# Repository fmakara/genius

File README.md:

# genius
Jogo Genius do Mural do PET

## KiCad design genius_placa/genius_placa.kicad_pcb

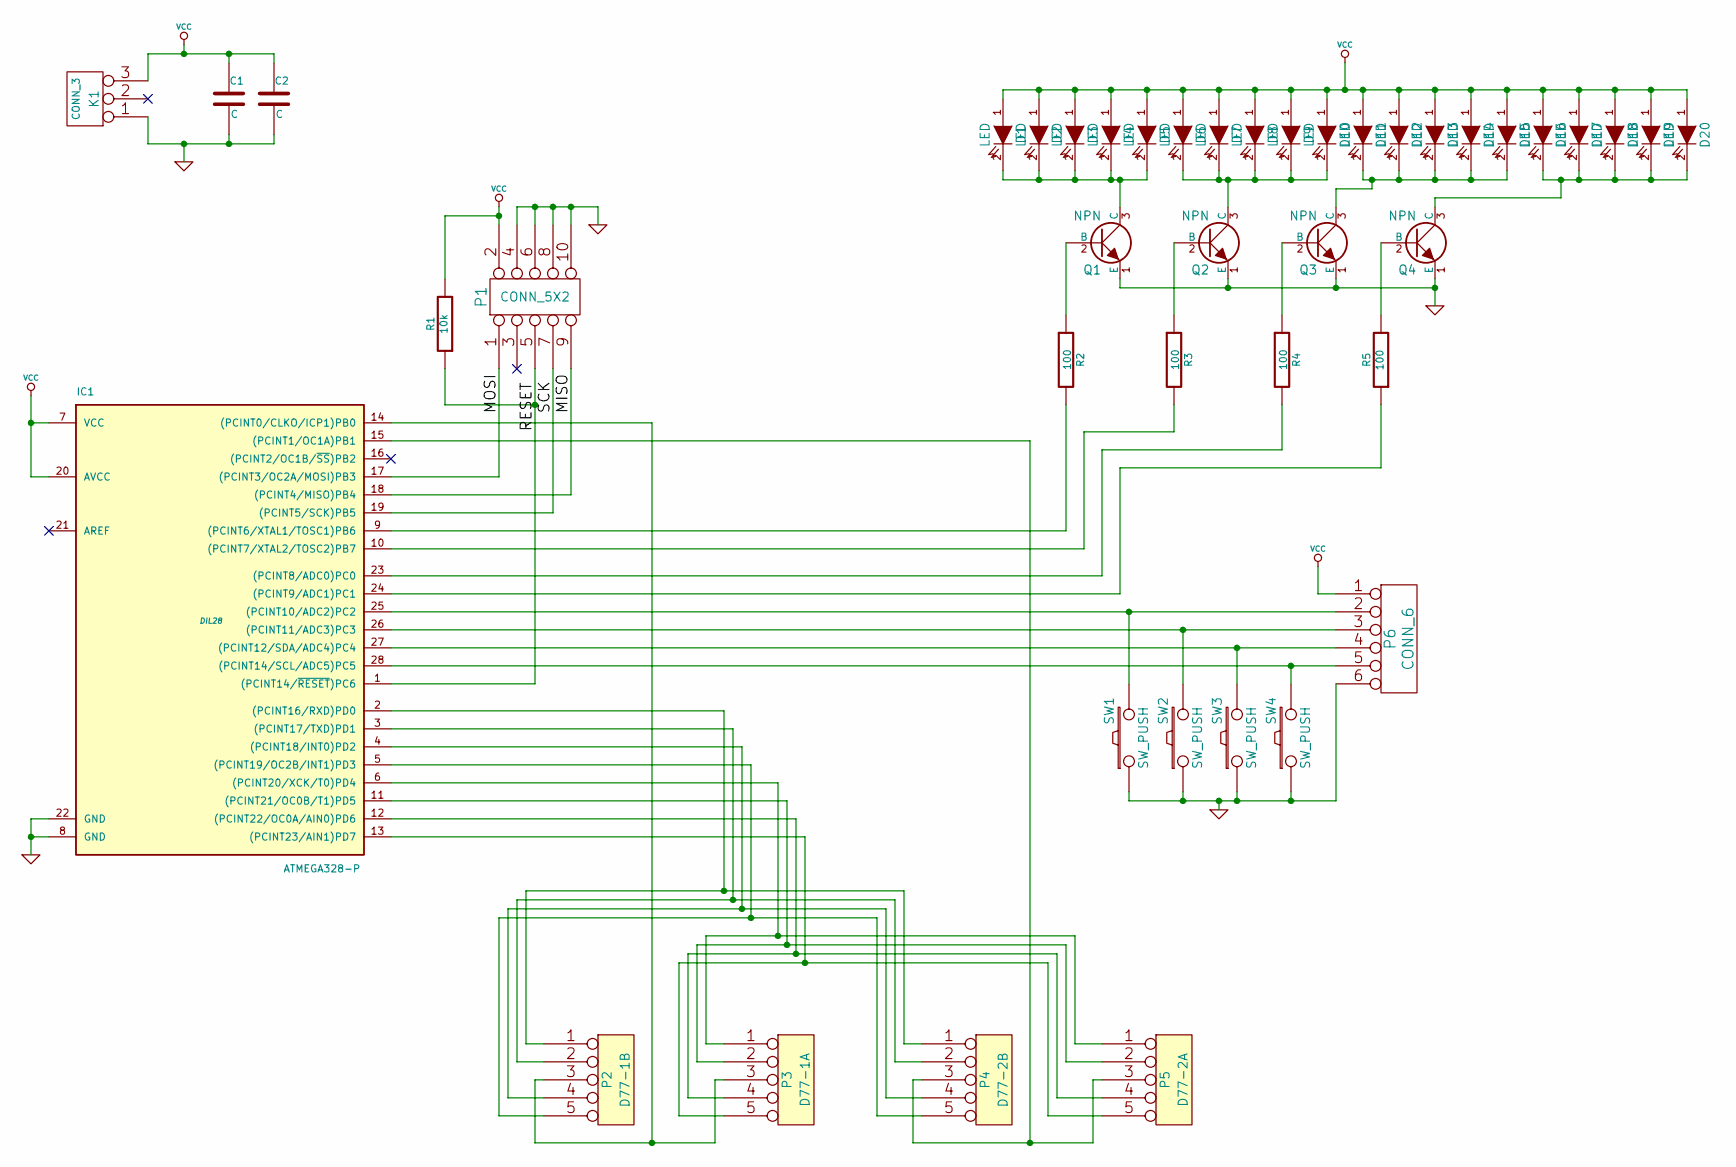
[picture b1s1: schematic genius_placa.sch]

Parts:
C1, C2: C
D1, D2, D3, D4, D5, D6, D7, D8, D9, D10, D11, D12, D13, D14, D15, D16, D17, D18, D19, D20: LED
IC1: ATMEGA328-P; DIL28
K1: CONN_3
P1: CONN_5X2
P2: D77-1B
P3: D77-1A
P4: D77-2B
P5: D77-2A
P6: CONN_6
Q1, Q2, Q3, Q4: NPN
R1: 10k
R2, R3, R4, R5: 100
SW1, SW2, SW3, SW4: SW_PUSH

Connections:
/MISO: IC1.18 ((PCINT4/MISO)PB4), P1.9
/MOSI: IC1.17 ((PCINT3/OC2A/MOSI)PB3), P1.1
/RESET: IC1.1 ((PCINT14/~RESET~)PC6), P1.5, R1.1
/SCK: IC1.19 ((PCINT5/SCK)PB5), P1.7
GND: C1.2, C2.2, IC1.8 (GND), IC1.22 (GND), K1.1, P1.4, P1.6, P1.8, P1.10, P6.6, Q1.1 (E), Q2.1 (E), Q3.1 (E), Q4.1 (E), SW1.1, SW2.1, SW3.1, SW4.1
unnamed: IC1.9 ((PCINT6/XTAL1/TOSC1)PB6), R2.2
unnamed: Q1.2 (B), R2.1
unnamed: Q2.2 (B), R3.1
unnamed: Q3.2 (B), R4.1
unnamed: Q4.2 (B), R5.2
unnamed: IC1.25 ((PCINT10/ADC2)PC2), P6.2, SW1.2
unnamed: IC1.26 ((PCINT11/ADC3)PC3), P6.3, SW2.2
unnamed: IC1.27 ((PCINT12/SDA/ADC4)PC4), P6.4, SW3.2
unnamed: IC1.24 ((PCINT9/ADC1)PC1), R5.1
unnamed: IC1.23 ((PCINT8/ADC0)PC0), R4.2
unnamed: IC1.10 ((PCINT7/XTAL2/TOSC2)PB7), R3.2
unnamed: D6.2 (K), D7.2 (K), D8.2 (K), D9.2 (K), D10.2 (K), Q2.3 (C)
unnamed: D1.2 (K), D2.2 (K), D3.2 (K), D4.2 (K), D5.2 (K), Q1.3 (C)
unnamed: D11.2 (K), D12.2 (K), D13.2 (K), D14.2 (K), D15.2 (K), Q3.3 (C)
unnamed: D16.2 (K), D17.2 (K), D18.2 (K), D19.2 (K), D20.2 (K), Q4.3 (C)
unnamed: IC1.12 ((PCINT22/OC0A/AIN0)PD6), P3.4, P5.4
unnamed: IC1.28 ((PCINT14/SCL/ADC5)PC5), P6.5, SW4.2
unnamed: IC1.13 ((PCINT23/AIN1)PD7), P3.5, P5.5
unnamed: IC1.6 ((PCINT20/XCK/T0)PD4), P3.1, P5.1
unnamed: IC1.5 ((PCINT19/OC2B/INT1)PD3), P2.5, P4.5
unnamed: IC1.3 ((PCINT17/TXD)PD1), P2.2, P4.2
unnamed: IC1.2 ((PCINT16/RXD)PD0), P2.1, P4.1
unnamed: IC1.14 ((PCINT0/CLKO/ICP1)PB0), P2.3, P3.3
unnamed: IC1.4 ((PCINT18/INT0)PD2), P2.4, P4.4
unnamed: IC1.11 ((PCINT21/OC0B/T1)PD5), P3.2, P5.2
unnamed: IC1.15 ((PCINT1/OC1A)PB1), P4.3, P5.3
VCC: C1.1, C2.1, D1.1 (A), D2.1 (A), D3.1 (A), D4.1 (A), D5.1 (A), D6.1 (A), D7.1 (A), D8.1 (A), D9.1 (A), D10.1 (A), D11.1 (A), D12.1 (A), D13.1 (A), D14.1 (A), D15.1 (A), D16.1 (A), D17.1 (A), D18.1 (A), D19.1 (A), D20.1 (A), IC1.7 (VCC), IC1.20 (AVCC), K1.3, P1.2, P6.1, R1.2

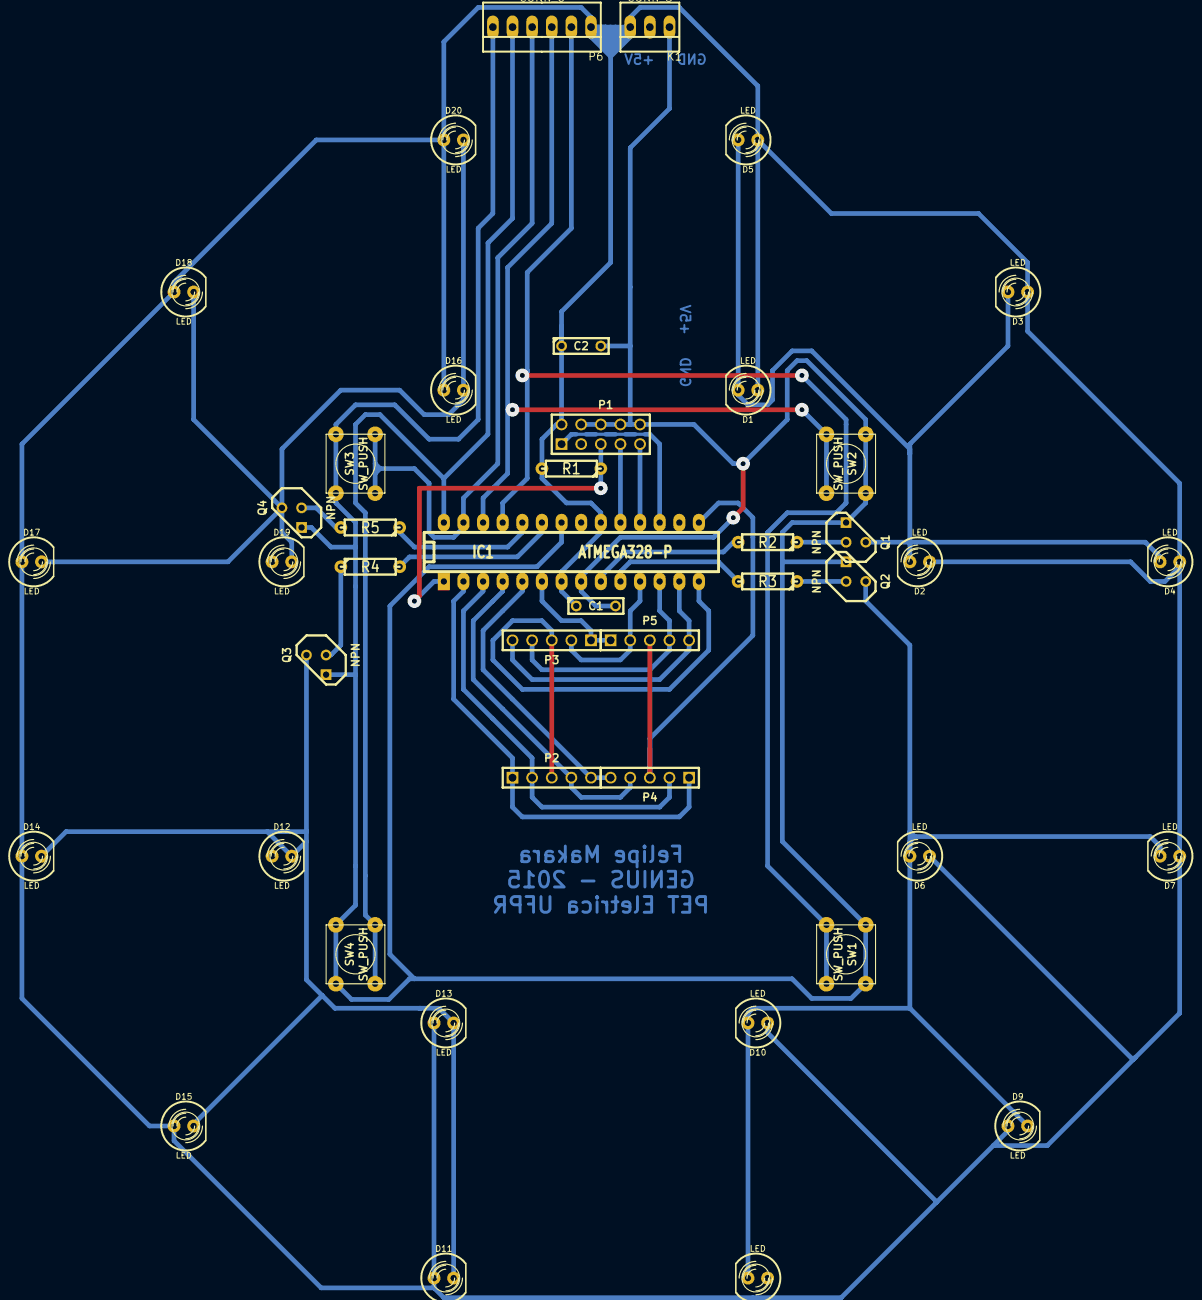
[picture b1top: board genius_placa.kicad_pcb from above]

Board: 2 copper layers, 43 parts (0 on the bottom side), 32 nets.

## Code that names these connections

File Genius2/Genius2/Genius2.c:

/*
 * Genius2.c
 *
 * Created: 31-Jul-15 10:36:23 AM
 *  Author: Felipe Makara
 */ 
#define F_CPU 4000000
#include <util/delay.h>
#include <avr/io.h>
#include <avr/interrupt.h>
#include <stdlib.h>
#include <avr/eeprom.h>

#define LED_VERDE PB7
#define LED_VERMELHO PC0
#define LED_AMARELO PB6
#define LED_AZUL PC1
#define BOTAO_VERDE PC2
#define BOTAO_VERMELHO PC5
#define BOTAO_AMARELO PC3
#define BOTAO_AZUL PC4

#define D7S_ANE PB1
#define D7S_AND PB0
#define D7S_AF PD2
#define D7S_BG PD3
#define D7S_CD PD5
#define D7S_DC PD6
#define D7S_EP PD7
#define D7S_FA PD1
#define D7S_GB PD0
#define D7S_PE PD4
//   a
// f   b
//   g
// e   c
//   d   p
uint8_t BUFF_D, BUFF_E;
void escreveNumero(int x){
	uint8_t dig_d[10] = {
		0b01110111, 0b01000001, 0b00111011, 0b01101011, 0b01001101,
		0b01101110, 0b01111110, 0b01000011, 0b01111111, 0b01101111
	};
	uint8_t dig_e[10] = {
		0b11101110, 0b00101000, 0b11001101, 0b01101101, 0b00101011, 
		0b01100111, 0b11100111, 0b00101100, 0b11101111, 0b01101111
	};
	int e, d, p;
	p = x/100;
	e = (x/10)%10;
	d = x%10;
	BUFF_D = dig_d[d];
	BUFF_E = dig_e[e];
	if(p==1)BUFF_D|= 1<<D7S_EP;
	if(p==2)BUFF_E|= 1<<D7S_PE;
}
void desenhaProgresso(int p){
	if(p==0xFF){
		BUFF_D = 0;
		BUFF_E = 0;
		return;
	}
	p = p%8;
	uint8_t es[8] = {0b00000100, 0b00000000, 0b00000000, 0b00000000, 0b00000000, 0b01000000, 0b10000000, 0b00000010};
	uint8_t ds[8] = {0b00000000, 0b00000010, 0b00000001, 0b01000000, 0b00100000, 0b00000000, 0b00000000, 0b00000000};
	BUFF_D = ds[p];
	BUFF_E = es[p];
}
void initPorts(){
	DDRB = 0b11000011;
	DDRC = 0b00000011;
	DDRD = 0b11111111;
	SFIOR &= ~(1<<PUD);
	PORTB = 0b00000011;
	PORTC = 0b00111100;
	PORTD = 0b00000000;
}
void initTimer2(){
	TCCR2 = 0b00000110;//8M/256 = 31250 / 256 = 122 int/s
	TIMSK |= (1<<TOIE2)|(1<<OCIE2);
	OCR2 = 128;
	BUFF_D = 0;
	BUFF_E = 0;
	sei();
}

uint8_t PWM[4], COUNT;
#define MAX_PWM 20
ISR(TIMER2_COMP_vect){
	PORTB |= (1<<D7S_ANE);
	PORTB &= ~(1<<D7S_AND);
	PORTD = BUFF_D;
}
ISR(TIMER2_OVF_vect){
	PORTB |= (1<<D7S_AND);
	PORTB &= ~(1<<D7S_ANE);
	PORTD = BUFF_E;
}
void initTimer0(){
	TCCR0 = 0b00000001;
	TIMSK |= (1<<TOIE0);
	PWM[0] = 0;
	PWM[1] = 0;
	PWM[2] = 0;
	PWM[3] = 0;
	COUNT = 0;
	sei();
}
ISR(TIMER0_OVF_vect){
	COUNT++;
	if(COUNT==255){
		COUNT = 0;
		if(PWM[0]>0) PORTB |= (1<<LED_VERDE);
		if(PWM[1]>0) PORTC |= (1<<LED_VERMELHO);
		if(PWM[2]>0) PORTC |= (1<<LED_AZUL);
		if(PWM[3]>0) PORTB |= (1<<LED_AMARELO);
	}
	if(COUNT>PWM[0]) PORTB &= ~(1<<LED_VERDE);
	if(COUNT>PWM[1]) PORTC &= ~(1<<LED_VERMELHO);
	if(COUNT>PWM[2]) PORTC &= ~(1<<LED_AZUL);
	if(COUNT>PWM[3]) PORTB &= ~(1<<LED_AMARELO);
}
uint8_t getButtonPress(int timeout){
	#define BOTAO_VERDE PC2
	#define BOTAO_VERMELHO PC5
	#define BOTAO_AMARELO PC3
	#define BOTAO_AZUL PC4
	uint16_t to = timeout;
	while(to>0){
		if(!(PINC&(1<<BOTAO_VERDE)))   {_delay_ms(20);return 0;}
		if(!(PINC&(1<<BOTAO_VERMELHO))){_delay_ms(20);return 1;}
		if(!(PINC&(1<<BOTAO_AZUL)))    {_delay_ms(20);return 2;}
		if(!(PINC&(1<<BOTAO_AMARELO))) {_delay_ms(20);return 3;}
		_delay_ms(10);
		to--;
	}
	return 0xFF;
}
void waitForRelease(uint8_t button){
	switch(button){
		case 0:
			while(!(PINC&(1<<BOTAO_VERDE)))_delay_ms(10);
			_delay_ms(100);
			break;
		case 1:
			while(!(PINC&(1<<BOTAO_VERMELHO)))_delay_ms(10);
			_delay_ms(100);
			break;
		case 2:
			while(!(PINC&(1<<BOTAO_AZUL)))_delay_ms(10);
			_delay_ms(100);
			break;
		case 3:
			while(!(PINC&(1<<BOTAO_AMARELO)))_delay_ms(10);
			_delay_ms(100);
			break;
	}
}
#define WINNER 250
#define VELOCIDADE_ULTIMO 800
#define VELOCIDADE_MAX 400
#define VELOCIDADE_MIN 800
#define VELOCIDADE_MEIO 5000
int genius(){
	uint8_t vetor[WINNER], perdeu = 0;
	int i, j, k, pont, v;
	for(i=0;i<WINNER;i++)vetor[i] = rand()%4;
	for(pont=3 ; pont<WINNER && !perdeu ; pont++){
		v = VELOCIDADE_MEIO/(pont-1);
		if(v>VELOCIDADE_MIN)v = VELOCIDADE_MIN;
		if(v<VELOCIDADE_MAX)v = VELOCIDADE_MAX;
		for(i=0;i<pont;i++){
			desenhaProgresso(i);
			for(j=0;j<(v>>1);j+=10){
				k = j>>1;
				if(k>MAX_PWM)k = MAX_PWM;
				PWM[vetor[i]] = k;
				_delay_ms(10);
			}
			for(j=0;j<(v>>1);j+=10){
				k = ((v>>1)-j)>>1;
				if(k>MAX_PWM)k = MAX_PWM;
				PWM[vetor[i]] = k;
				_delay_ms(10);
			}
			PWM[vetor[i]] = 0;
		}
		desenhaProgresso(i);
		for(j=0;j<(VELOCIDADE_ULTIMO>>1);j+=10){
			k = j>>1;
			if(k>MAX_PWM)k = MAX_PWM;
			PWM[vetor[i]] = k;
			_delay_ms(10);
		}
		for(j=0;j<(VELOCIDADE_ULTIMO>>1);j+=10){
			k = ((VELOCIDADE_ULTIMO>>1)-j)>>1;
			if(k>MAX_PWM)k = MAX_PWM;
			PWM[vetor[i]] = k;
			_delay_ms(10);
		}
		PWM[vetor[i]] = 0;
		escreveNumero(pont);
		for(i=0;i<pont+1 && !perdeu;i++){
			j = getButtonPress(2000);
			_delay_ms(100);
			if(j!=vetor[i]){
				perdeu = 1;
				PWM[0]=MAX_PWM;PWM[1]=MAX_PWM;PWM[2]=MAX_PWM;PWM[3]=MAX_PWM;
				_delay_ms(300);
				PWM[0]=0;PWM[1]=0;PWM[2]=0;PWM[3]=0;
				_delay_ms(300);
				PWM[0]=MAX_PWM;PWM[1]=MAX_PWM;PWM[2]=MAX_PWM;PWM[3]=MAX_PWM;
				_delay_ms(300);
				PWM[0]=0;PWM[1]=0;PWM[2]=0;PWM[3]=0;
				_delay_ms(300);
				PWM[0]=MAX_PWM;PWM[1]=MAX_PWM;PWM[2]=MAX_PWM;PWM[3]=MAX_PWM;
				_delay_ms(300);
				PWM[0]=0;PWM[1]=0;PWM[2]=0;PWM[3]=0;
				_delay_ms(300);
				PWM[0]=MAX_PWM;PWM[1]=MAX_PWM;PWM[2]=MAX_PWM;PWM[3]=MAX_PWM;
				_delay_ms(300);
				PWM[0]=0;PWM[1]=0;PWM[2]=0;PWM[3]=0;
				_delay_ms(300);
				PWM[0]=MAX_PWM;PWM[1]=MAX_PWM;PWM[2]=MAX_PWM;PWM[3]=MAX_PWM;
				_delay_ms(300);
				PWM[0]=0;PWM[1]=0;PWM[2]=0;PWM[3]=0;
				_delay_ms(300);
			}else{
				if(i==pont)escreveNumero(pont+1);
				PWM[j] = MAX_PWM;
				waitForRelease(j);
				PWM[j] = 0;
			}
		}
		_delay_ms(1000);
	}
	return pont-1;
}
int idle(){
	int gira = 0, b;
	while(1){
		b = getButtonPress(30);
		if(b==0xFF){
			gira++;
			PWM[0]=0;PWM[1]=0;PWM[2]=0;PWM[3]=0;
			PWM[gira%4]=MAX_PWM;
		}else{
			PWM[0]=0;PWM[1]=0;PWM[2]=0;PWM[3]=0;
			waitForRelease(b);
			return (gira<<2)+b;
		}
	}
}


int main(void){
	int pontuacao, maxima;
	initPorts();
	initTimer0();
	initTimer2();
	maxima = eeprom_read_byte(0); 
	if(maxima<3 || maxima==0xFF){
		maxima = 3;
		eeprom_write_byte(0,maxima);
	}
	escreveNumero(maxima);
	srand(idle());
	while(1){
		pontuacao = genius();
		if(pontuacao>maxima){
			maxima = pontuacao;
			eeprom_write_byte(0,maxima);
		}
		escreveNumero(maxima);
		idle();
	}
}

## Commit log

2016-06-09 Completo
